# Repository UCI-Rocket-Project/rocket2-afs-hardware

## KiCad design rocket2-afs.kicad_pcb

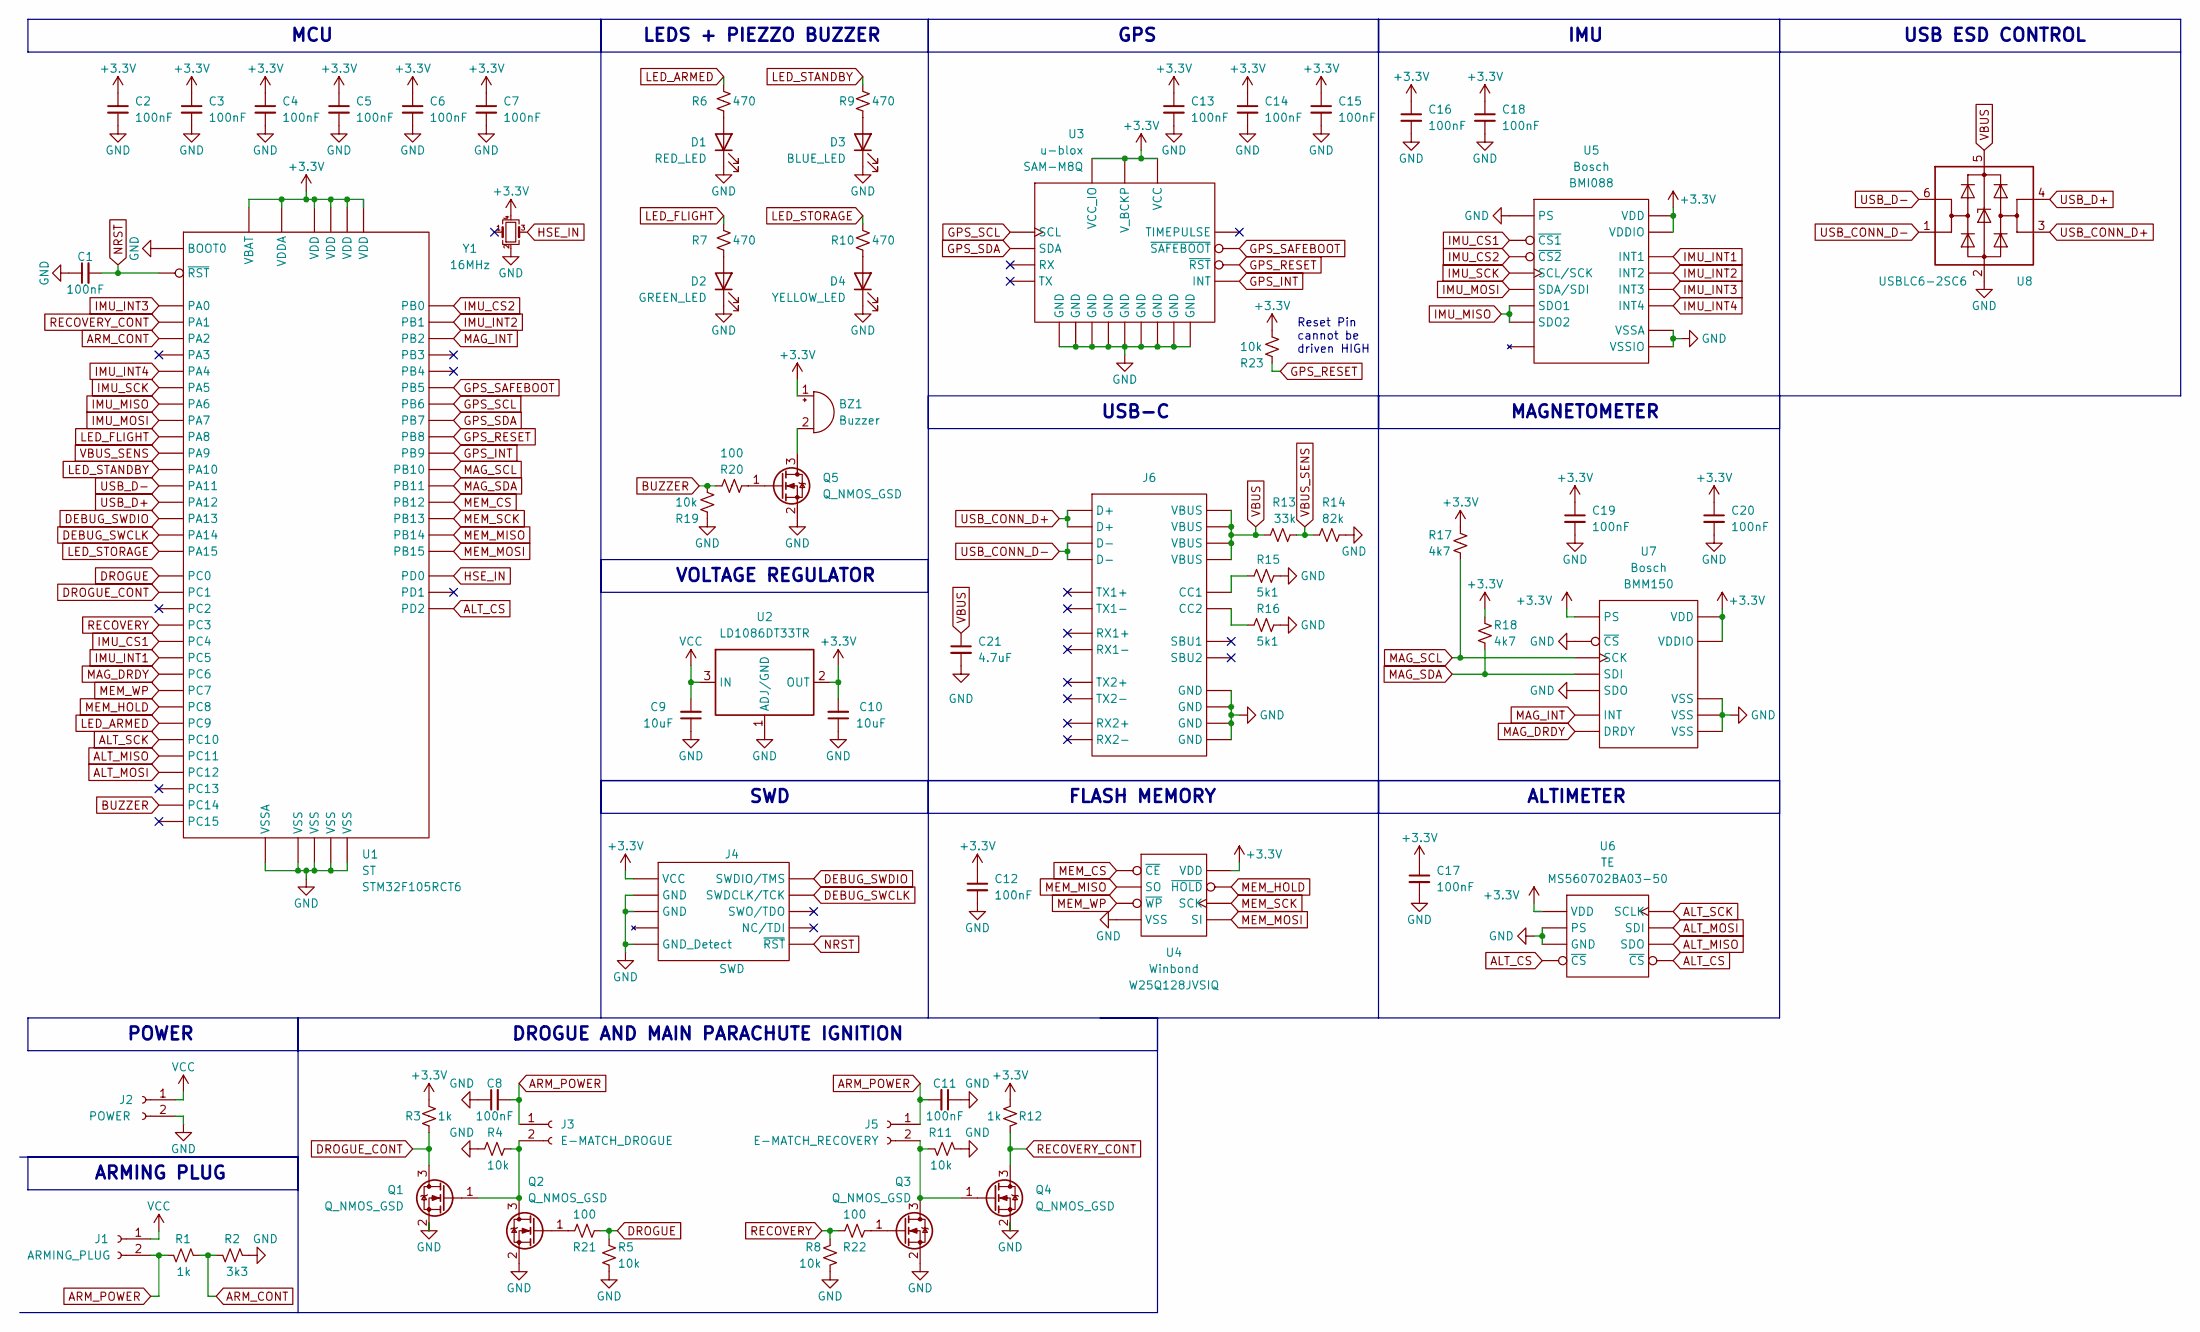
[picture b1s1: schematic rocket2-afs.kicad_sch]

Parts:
BZ1: Buzzer; Buzzer_CUI_CPT-9019S-SMT; Part # CMI-9653S-SMT-TR
C1, C2, C3, C4, C5, C6, C7, C8, C11, C12, C13, C14, C15, C16, C17, C18, C19, C20: 100nF; C_0603_1608Metric; Part # Generic 0603 6.3V 100nF X7R MLCC
C9, C10: 10uF; C_0603_1608Metric; Part # Generic 0603 6.3V 10uF X7R MLCC
C21: 4.7uF; C_0603_1608Metric; Part # Generic 0603 6.3V 4.7uF X7R MLCC
D1: RED_LED; D_0603_1608Metric; Part # Generic Red LED
D2: GREEN_LED; D_0603_1608Metric; Part # Generic Green LED
D3: BLUE_LED; D_0603_1608Metric; Part # Generic Blue LED
D4: YELLOW_LED; D_0603_1608Metric; Part # Generic Yellow LED
J1: ARMING_PLUG; TerminalBlock_bornier-2_P5.08mm; Part # Generic Horizontal TH P5.08mm Screw Fas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
J2: POWER; TerminalBlock_bornier-2_P5.08mm; Part # Generic Horizontal TH P5.08mm Screw Fas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
J3: E-MATCH_DROGUE; TerminalBlock_bornier-2_P5.08mm; Part # Generic Horizontal TH P5.08mm Screw Fas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
J4: SWD; PinHeader_2x05_P1.27mm_Vertical_SMD; Part # Generic 2x05 P1.27mm Vertical Pin Heade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
J5: E-MATCH_RECOVERY; TerminalBlock_bornier-2_P5.08mm; Part # Generic Horizontal TH P5.08mm Screw Fas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
J6: USB_C_Receptacle_GCT_USB4105-xx-A_16P_TopMnt_Horizontal; Part # USB4105-GF-A
Q1, Q2, Q3, Q4, Q5: Q_NMOS_GSD; TSOT-23; Part # PMV30UN2
R1, R3, R12: 1k; R_0603_1608Metric; Part # Generic 0603 1k 1% Resistor
R2: 3k3; R_0603_1608Metric; Part # Generic 0603 3.3k 1% Resistor
R4, R5, R8, R11, R19, R23: 10k; R_0603_1608Metric; Part # Generic 0603 10k 1% Resistor
R6, R7, R9, R10: 470; R_0603_1608Metric; Part # Generic 0603 470 1% Resistor
R13: 33k; R_0603_1608Metric; Part # Generic 0603 33k 1% Resistor
R14: 82k; R_0603_1608Metric; Part # Generic 0603 82k 1% Resistor
R15, R16: 5k1; R_0603_1608Metric; Part # Generic 0603 5.1k 1% Resistor
R17, R18: 4k7; R_0603_1608Metric; Part # Generic 0603 4.7k 1% Resistor
R20, R21, R22: 100; R_0603_1608Metric; Part # Generic 0603 100 1% Resistor
U1: LQFP-64_10x10mm_P0.5mm; Part # STM32F105RCT6
U2: LD1086DT33TR; TO-252-2; Part # LD1086DT33TR
U3: ublox_SAM-M8Q; Part # SAM-M8Q
U4: SOIC-8W_5.3x5.3mm_P1.27mm; Part # W25Q128JVSIQ
U5: BMI088; Part # BMI088
U6: MS5607-02BA; Part # MS560702BA03-50
U7: WLCSP-12_1.56x1.56mm_P0.4mm; Part # BMM150
U8: USBLC6-2SC6; SOT-23-6; Part # USBLC6-2SC6
Y1: 16MHz; Crystal_SMD_2520-4Pin_2.5x2.0mm; Part # ECS-1633-160-BN-TR

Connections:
+3.3V: BZ1.1 (+), C2.1, C3.1, C4.1, C5.1, C6.1, C7.1, C10.2, C12.1, C13.1, C14.1, C15.1, C16.1, C17.1, C18.1, C19.1, C20.1, J4.1 (VCC), R3.1, R12.1, R17.1, R18.1, R23.1, U1.1 (VBAT), U1.13 (VDDA), U1.19 (VDD), U1.32 (VDD), U1.48 (VDD), U1.64 (VDD), U2.2 (OUT), U3.2 (VCC_IO), U3.3 (V_BCKP), U3.17 (VCC), U4.8 (VDD), U5.3 (VDD), U5.11 (VDDIO), U6.1 (VDD), U7.A1 (PS), U7.B2 (VDDIO), U7.E5 (VDD), Y1.4
ALT_CS: U1.54 (PD2), U6.4 (~CS), U6.5 (~CS)
ALT_MISO: U1.52 (PC11), U6.6 (SDO)
ALT_MOSI: U1.53 (PC12), U6.7 (SDI)
ALT_SCK: U1.51 (PC10), U6.8 (SCLK)
ARM_CONT: R1.2, R2.1, U1.16 (PA2)
ARM_POWER: C8.2, C11.2, J1.2, J3.1, J5.1, R1.1
BUZZER: R19.1, R20.1, U1.3 (PC14)
DEBUG_SWCLK: J4.4 (SWDCLK/TCK), U1.49 (PA14)
DEBUG_SWDIO: J4.2 (SWDIO/TMS), U1.46 (PA13)
DROGUE: R5.1, R21.2, U1.8 (PC0)
DROGUE_CONT: Q1.3 (D), R3.2, U1.9 (PC1)
GND: C1.1, C2.2, C3.2, C4.2, C5.2, C6.2, C7.2, C8.1, C9.1, C10.1, C11.1, C12.2, C13.2, C14.2, C15.2, C16.2, C17.2, C18.2, C19.2, C20.2, C21.2, D1.1 (K), D2.1 (K), D3.1 (K), D4.1 (K), J2.2, J4.3 (GND), J4.5 (GND), J4.9 (GND_Detect), J6.A1 (GND), J6.A12 (GND), J6.B1 (GND), J6.B12 (GND), Q1.2 (S), Q2.2 (S), Q3.2 (S), Q4.2 (S), Q5.2 (S), R2.2, R4.2, R5.2, R8.2, R11.2, R14.1, R15.1, R16.1, R19.2, U1.12 (VSSA), U1.18 (VSS), U1.31 (VSS), U1.47 (VSS), U1.60 (BOOT0), U1.63 (VSS), U2.1 (ADJ/GND), U3.1 (GND), U3.4 (GND), U3.5 (GND), U3.6 (GND), U3.10 (GND), U3.11 (GND), U3.15 (GND), U3.16 (GND), U3.20 (GND), U4.4 (VSS), U5.4 (VSSA), U5.6 (VSSIO), U5.7 (PS), U6.2 (PS), U6.3 (GND), U7.A5 (~CS), U7.C1 (SDO), U7.C5 (VSS), U7.E1 (VSS), U7.E3 (VSS), U8.2 (GND), Y1.2
GPS_INT: U1.62 (PB9), U3.19 (INT)
GPS_RESET: R23.2, U1.61 (PB8), U3.18 (~RST)
GPS_SAFEBOOT: U1.57 (PB5), U3.8 (~SAFEBOOT)
GPS_SCL: U1.58 (PB6), U3.12 (SCL)
GPS_SDA: U1.59 (PB7), U3.9 (SDA)
HSE_IN: U1.5 (PD0), Y1.3
IMU_CS1: U1.24 (PC4), U5.14 (~CS1)
IMU_CS2: U1.26 (PB0), U5.5 (~CS2)
IMU_INT1: U1.25 (PC5), U5.16 (INT1)
IMU_INT2: U1.27 (PB1), U5.1 (INT2)
IMU_INT3: U1.14 (PA0), U5.12 (INT3)
IMU_INT4: U1.20 (PA4), U5.13 (INT4)
IMU_MISO: U1.22 (PA6), U5.10 (SDO2), U5.15 (SDO1)
IMU_MOSI: U1.23 (PA7), U5.9 (SDA/SDI)
IMU_SCK: U1.21 (PA5), U5.8 (SCL/SCK)
LED_ARMED: R6.1, U1.40 (PC9)
LED_FLIGHT: R7.1, U1.41 (PA8)
LED_STANDBY: R9.1, U1.43 (PA10)
LED_STORAGE: R10.1, U1.50 (PA15)
MAG_DRDY: U1.37 (PC6), U7.D4 (DRDY)
MAG_INT: U1.28 (PB2), U7.D2 (INT)
MAG_SCL: R17.2, U1.29 (PB10), U7.A3 (SCK)
MAG_SDA: R18.2, U1.30 (PB11), U7.B4 (SDI)
MEM_CS: U1.33 (PB12), U4.1 (~CE)
MEM_HOLD: U1.39 (PC8), U4.7 (~HOLD)
MEM_MISO: U1.35 (PB14), U4.2 (SO)
MEM_MOSI: U1.36 (PB15), U4.5 (SI)
MEM_SCK: U1.34 (PB13), U4.6 (SCK)
MEM_WP: U1.38 (PC7), U4.3 (~WP)
NRST: C1.2, J4.10 (~RST), U1.7 (~RST)
unnamed: BZ1.2 (-), Q5.3 (D)
unnamed: D1.2 (A), R6.2
unnamed: D2.2 (A), R7.2
unnamed: D3.2 (A), R9.2
unnamed: D4.2 (A), R10.2
unnamed: J3.2, Q1.1 (G), Q2.3 (D), R4.1
unnamed: J5.2, Q3.3 (D), Q4.1 (G), R11.1
unnamed: J6.A5 (CC1), R15.2
unnamed: J6.B5 (CC2), R16.2
unnamed: Q2.1 (G), R21.1
unnamed: Q3.1 (G), R22.2
unnamed: Q5.1 (G), R20.2
RECOVERY: R8.1, R22.1, U1.11 (PC3)
RECOVERY_CONT: Q4.3 (D), R12.2, U1.15 (PA1)
USB_CONN_D+: J6.A6 (D+), J6.B6 (D+), U8.3 (I/O2)
USB_CONN_D-: J6.A7 (D-), J6.B7 (D-), U8.1 (I/O1)
USB_D+: U1.45 (PA12), U8.4 (I/O2)
USB_D-: U1.44 (PA11), U8.6 (I/O1)
VBUS: C21.1, J6.A4 (VBUS), J6.A9 (VBUS), J6.B4 (VBUS), J6.B9 (VBUS), R13.1, U8.5 (VBUS)
VBUS_SENS: R13.2, R14.2, U1.42 (PA9)
VCC: C9.2, J1.1, J2.1, U2.3 (IN)

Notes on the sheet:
POWER
USB ESD CONTROL
ARMING PLUG
SWD
MCU
ALTIMETER
Reset Pin cannot be driven HIGH
GPS
IMU
MAGNETOMETER
FLASH MEMORY
USB-C
LEDS + PIEZZO BUZZER
DROGUE AND MAIN PARACHUTE IGNITION
VOLTAGE REGULATOR

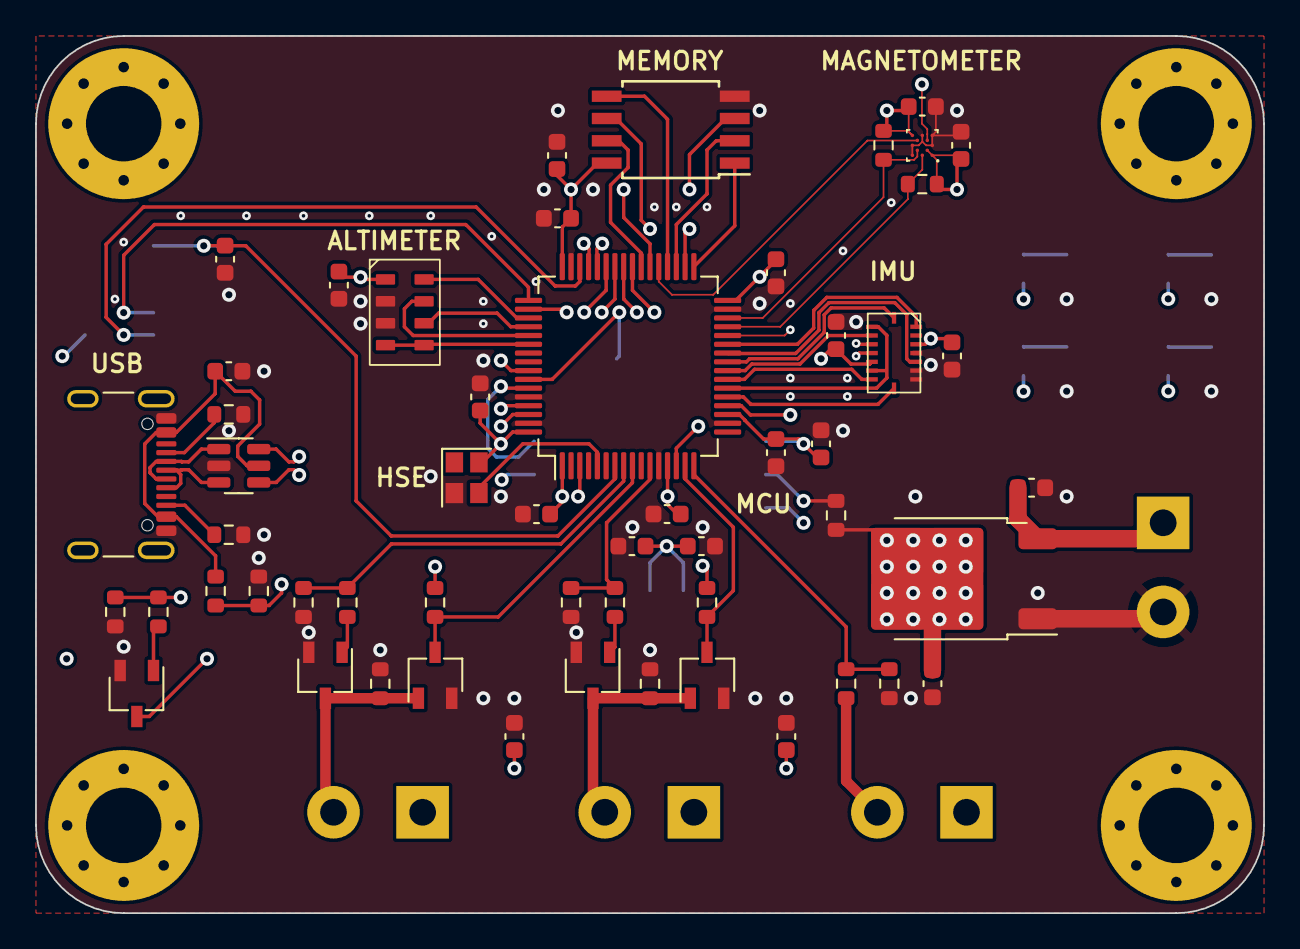
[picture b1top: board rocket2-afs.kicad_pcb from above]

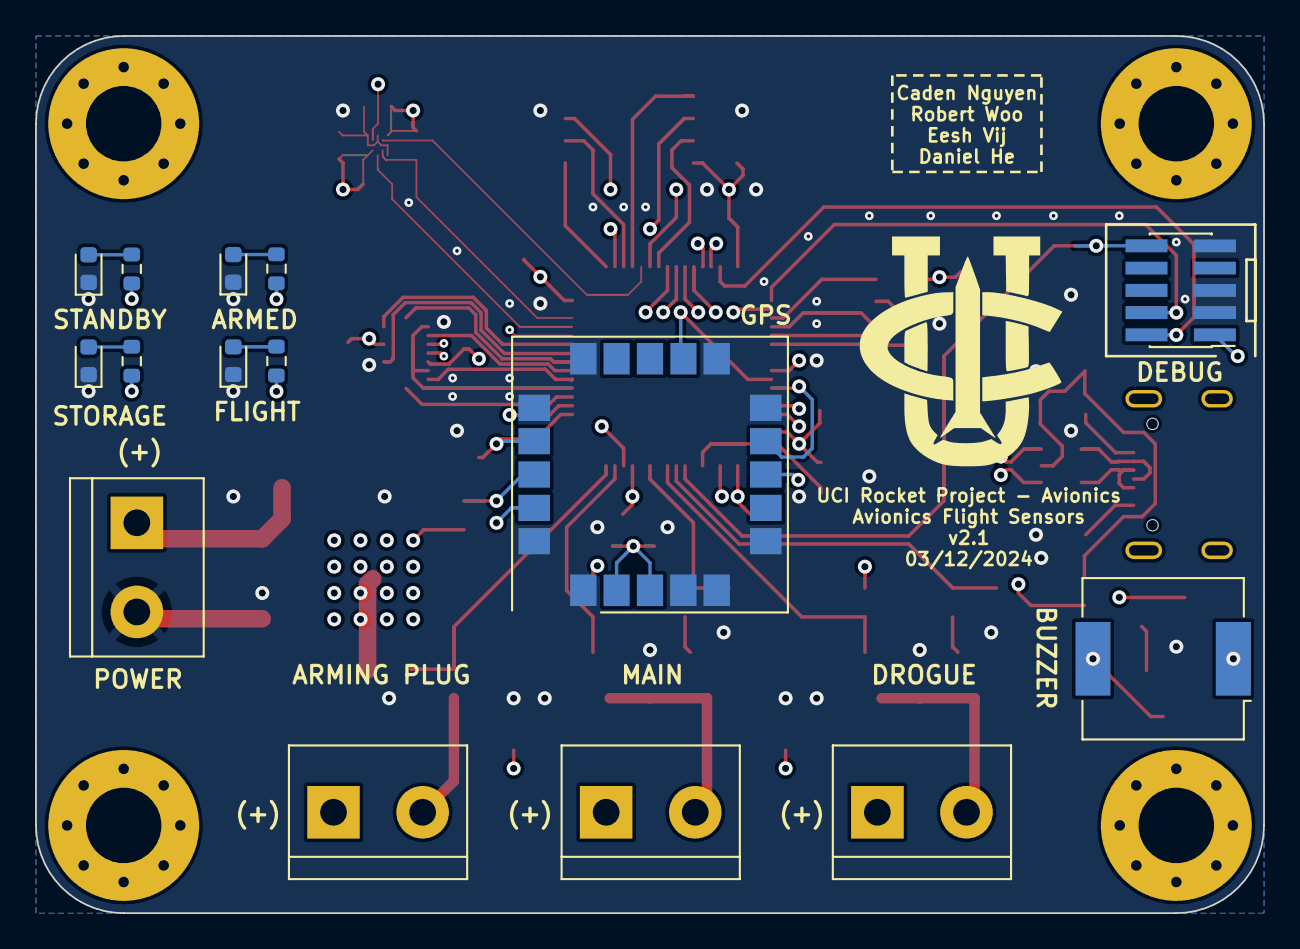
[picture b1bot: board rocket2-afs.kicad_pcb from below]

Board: 4 copper layers, 70.0 x 50.0 mm, 69 parts (15 on the bottom side), 64 nets.

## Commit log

2024-02-08 Finalized Schematic. PCB is WIP by 02-11-2024
2024-02-11 Fixed HSE pinout. Updated Crystal circuit.
2024-02-12 Adjusted Symbol Libraries for USB-C and Piezo Buzzer
2024-02-14 New MI-9653S-SMT-TR Buzzer and Buzzer Circuit. Added power footprint.
2024-02-21 Complete PCB, first iteration
2024-02-26 Current limiting resistors to MOSFETs. Silkscreen names + Logo. Adjusted BMI088 footprint as per ERC error (LOCAL TO PCB).
2024-02-29 wrote in comments
2024-03-04 Adjusted to M4 Screws
2024-03-06 Completely Remade PCB to adjust for GPS GND Shield
2024-03-11 Silkscreen Changes for Readability
2024-03-12 Completely Remade PCB to Space out Components
2024-03-13 Moved All Thick Components to "Front" Layer. Added Silkscreens
2024-03-13 Silkscreen update.
2024-03-13 Adjusted VBUS
2024-03-13 Moved BOOT0 Schematic to RST
2024-03-13 Updated Generic Component Assignment
2024-03-13 Removed .lck files
2024-03-13 Silkscreen for debugger
2024-03-14 Updated Generic Component Descriptions
2024-03-14 Changed Debug Symbol to UCIRP-L Library footrpint
2024-03-14 Final tweaks
2024-08-27 Added GPS RESET pullup resistor to PCB
